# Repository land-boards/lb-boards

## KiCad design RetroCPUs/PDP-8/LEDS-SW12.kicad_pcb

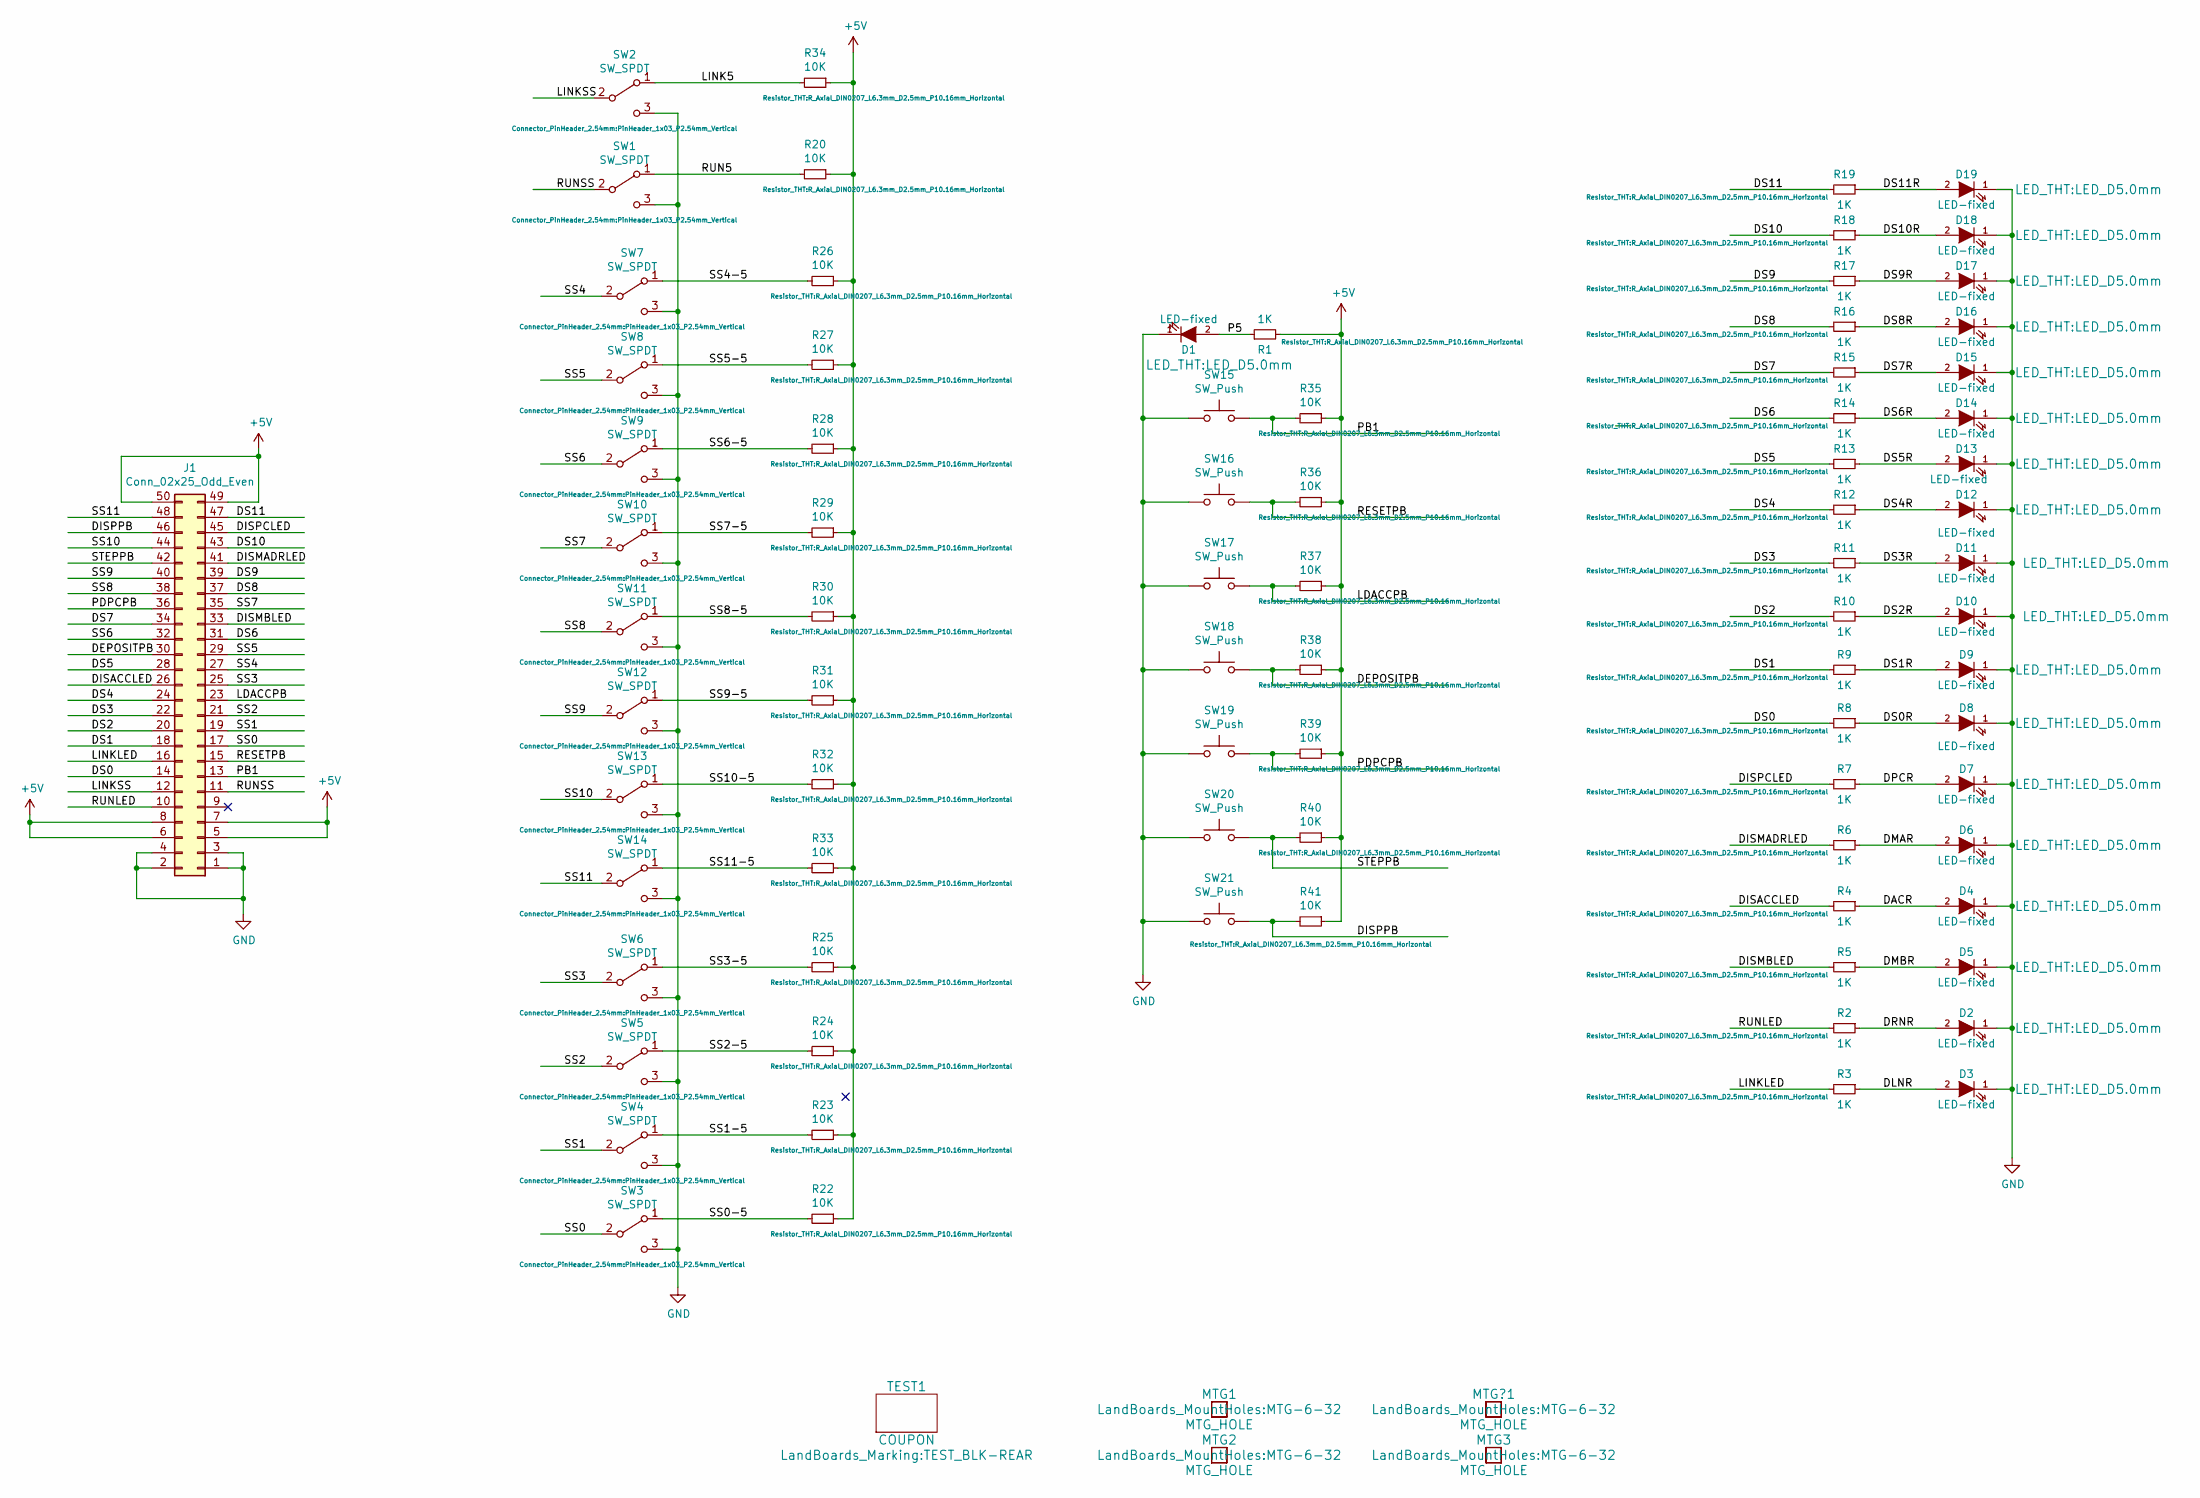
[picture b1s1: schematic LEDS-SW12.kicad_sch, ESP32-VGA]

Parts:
D1, D2, D3, D4, D5, D6, D7, D8, D9, D10, D11, D12, D13, D14, D15, D16, D17, D18, D19: LED-fixed; LED_D5.0mm
J1: Conn_02x25_Odd_Even; PinHeader_2x25_P2.54mm_Horizontal
MTG1, MTG2, MTG3: MTG_HOLE; MTG-6-32
MTG?1: MTG_HOLE; MTG-6-32
R1, R2, R3, R4, R5, R6, R7, R8, R9, R10, R11, R12, R13, R14, R15, R16, R17, R18, R19: 1K; R_Axial_DIN0207_L6.3mm_D2.5mm_P10.16mm_Horizontal
R20, R22, R23, R24, R25, R26, R27, R28, R29, R30, R31, R32, R33, R34, R35, R36, R37, R38, R39, R40, R41: 10K; R_Axial_DIN0207_L6.3mm_D2.5mm_P10.16mm_Horizontal
SW1, SW2, SW3, SW4, SW5, SW6, SW7, SW8, SW9, SW10, SW11, SW12, SW13, SW14: SW_SPDT; PinHeader_1x03_P2.54mm_Vertical
SW15, SW16, SW17, SW18, SW19, SW20, SW21: SW_Push; SW_PUSH_6mm_H8.5mm
TEST1: COUPON; TEST_BLK-REAR

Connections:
+5V: J1.5, J1.6, J1.7, J1.8, J1.49, J1.50, R1.2, R20.1, R22.1, R23.1, R24.1, R25.1, R26.1, R27.1, R28.1, R29.1, R30.1, R31.1, R32.1, R33.1, R34.1, R35.1, R36.1, R37.1, R38.1, R39.1, R40.1, R41.1
/DACR: D4.2 (A), R4.1
/DEPOSITPB: J1.30, R38.2, SW18.2
/DISACCLED: J1.26, R4.2
/DISMADRLED: J1.41, R6.2
/DISMBLED: J1.33, R5.2
/DISPCLED: J1.45, R7.2
/DISPPB: J1.46, R41.2, SW21.2
/DLNR: D3.2 (A), R3.1
/DMAR: D6.2 (A), R6.1
/DMBR: D5.2 (A), R5.1
/DPCR: D7.2 (A), R7.1
/DRNR: D2.2 (A), R2.1
/DS0: J1.14, R8.2
/DS0R: D8.2 (A), R8.1
/DS1: J1.18, R9.2
/DS1R: D9.2 (A), R9.1
/DS2: J1.20, R10.2
/DS2R: D10.2 (A), R10.1
/DS3: J1.22, R11.2
/DS3R: D11.2 (A), R11.1
/DS4: J1.24, R12.2
/DS4R: D12.2 (A), R12.1
/DS5: J1.28, R13.2
/DS5R: D13.2 (A), R13.1
/DS6: J1.31, R14.2
/DS6R: D14.2 (A), R14.1
/DS7: J1.34, R15.2
/DS7R: D15.2 (A), R15.1
/DS8: J1.37, R16.2
/DS8R: D16.2 (A), R16.1
/DS9: J1.39, R17.2
/DS9R: D17.2 (A), R17.1
/DS10: J1.43, R18.2
/DS10R: D18.2 (A), R18.1
/DS11: J1.47, R19.2
/DS11R: D19.2 (A), R19.1
/LDACCPB: J1.23, R37.2, SW17.2
/LINK5: R34.2, SW2.1 (A)
/LINKLED: J1.16, R3.2
/LINKSS: J1.12, SW2.2 (B)
/P5: D1.2 (A), R1.1
/PB1: J1.13, R35.2, SW15.2
/PDPCPB: J1.36, R39.2, SW19.2
/RESETPB: J1.15, R36.2, SW16.2
/RUN5: R20.2, SW1.1 (A)
/RUNLED: J1.10, R2.2
/RUNSS: J1.11, SW1.2 (B)
/SS0: J1.17, SW3.2 (B)
/SS0-5: R22.2, SW3.1 (A)
/SS1: J1.19, SW4.2 (B)
/SS1-5: R23.2, SW4.1 (A)
/SS2: J1.21, SW5.2 (B)
/SS2-5: R24.2, SW5.1 (A)
/SS3: J1.25, SW6.2 (B)
/SS3-5: R25.2, SW6.1 (A)
/SS4: J1.27, SW7.2 (B)
/SS4-5: R26.2, SW7.1 (A)
/SS5: J1.29, SW8.2 (B)
/SS5-5: R27.2, SW8.1 (A)
/SS6: J1.32, SW9.2 (B)
/SS6-5: R28.2, SW9.1 (A)
/SS7: J1.35, SW10.2 (B)
/SS7-5: R29.2, SW10.1 (A)
/SS8: J1.38, SW11.2 (B)
/SS8-5: R30.2, SW11.1 (A)
/SS9: J1.40, SW12.2 (B)
/SS9-5: R31.2, SW12.1 (A)
/SS10: J1.44, SW13.2 (B)
/SS10-5: R32.2, SW13.1 (A)
/SS11: J1.48, SW14.2 (B)
/SS11-5: R33.2, SW14.1 (A)
/STEPPB: J1.42, R40.2, SW20.2
GND: D1.1 (K), D2.1 (K), D3.1 (K), D4.1 (K), D5.1 (K), D6.1 (K), D7.1 (K), D8.1 (K), D9.1 (K), D10.1 (K), D11.1 (K), D12.1 (K), D13.1 (K), D14.1 (K), D15.1 (K), D16.1 (K), D17.1 (K), D18.1 (K), D19.1 (K), J1.1, J1.2, J1.3, J1.4, SW1.3 (C), SW2.3 (C), SW3.3 (C), SW4.3 (C), SW5.3 (C), SW6.3 (C), SW7.3 (C), SW8.3 (C), SW9.3 (C), SW10.3 (C), SW11.3 (C), SW12.3 (C), SW13.3 (C), SW14.3 (C), SW15.1, SW16.1, SW17.1, SW18.1, SW19.1, SW20.1, SW21.1

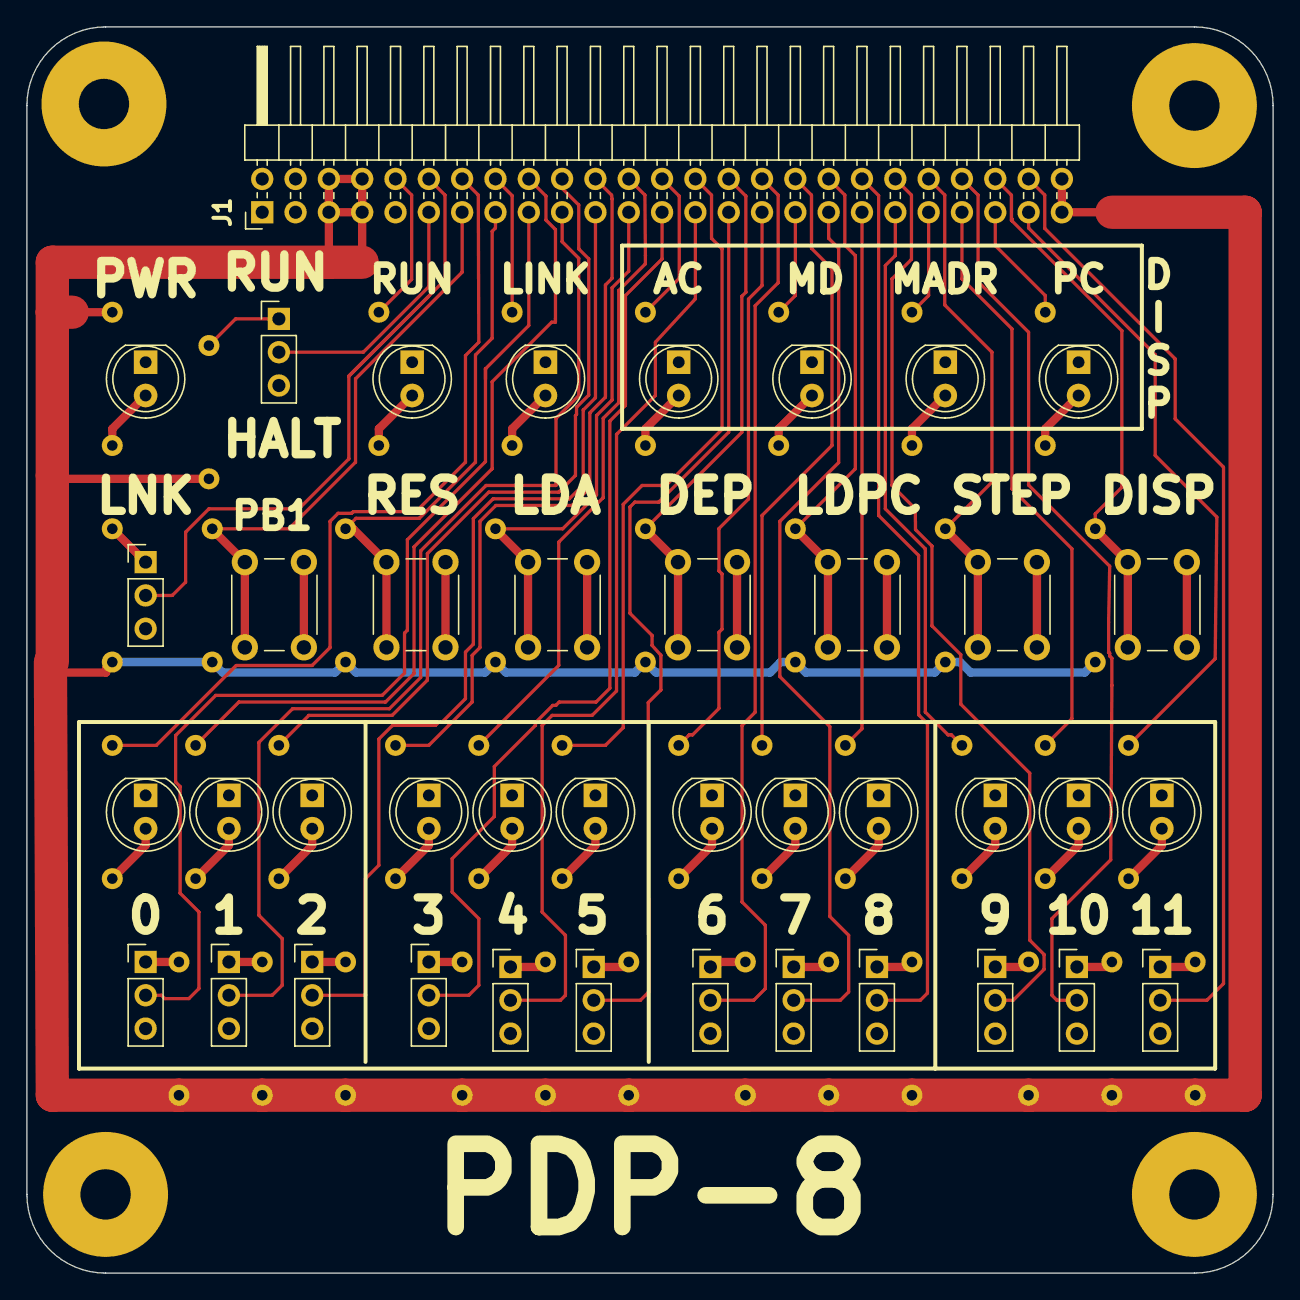
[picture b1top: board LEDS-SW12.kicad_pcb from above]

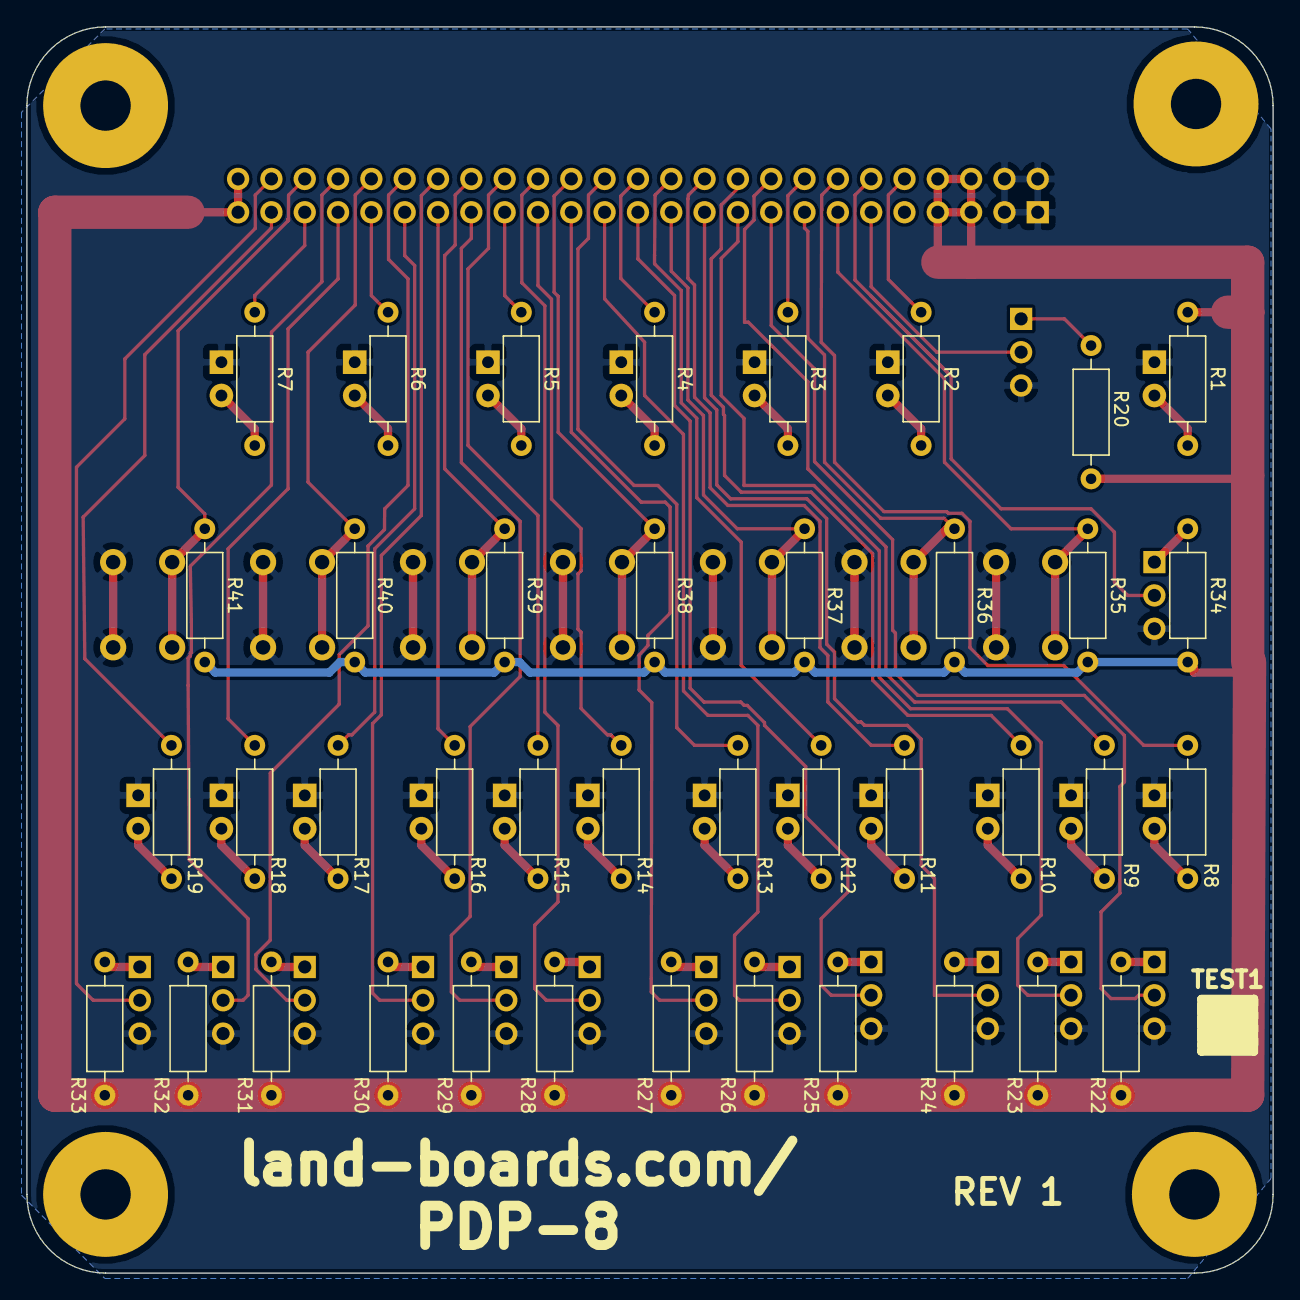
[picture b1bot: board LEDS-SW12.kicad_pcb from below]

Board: 2 copper layers, 95.0 x 95.0 mm, 86 parts (40 on the bottom side), 74 nets.

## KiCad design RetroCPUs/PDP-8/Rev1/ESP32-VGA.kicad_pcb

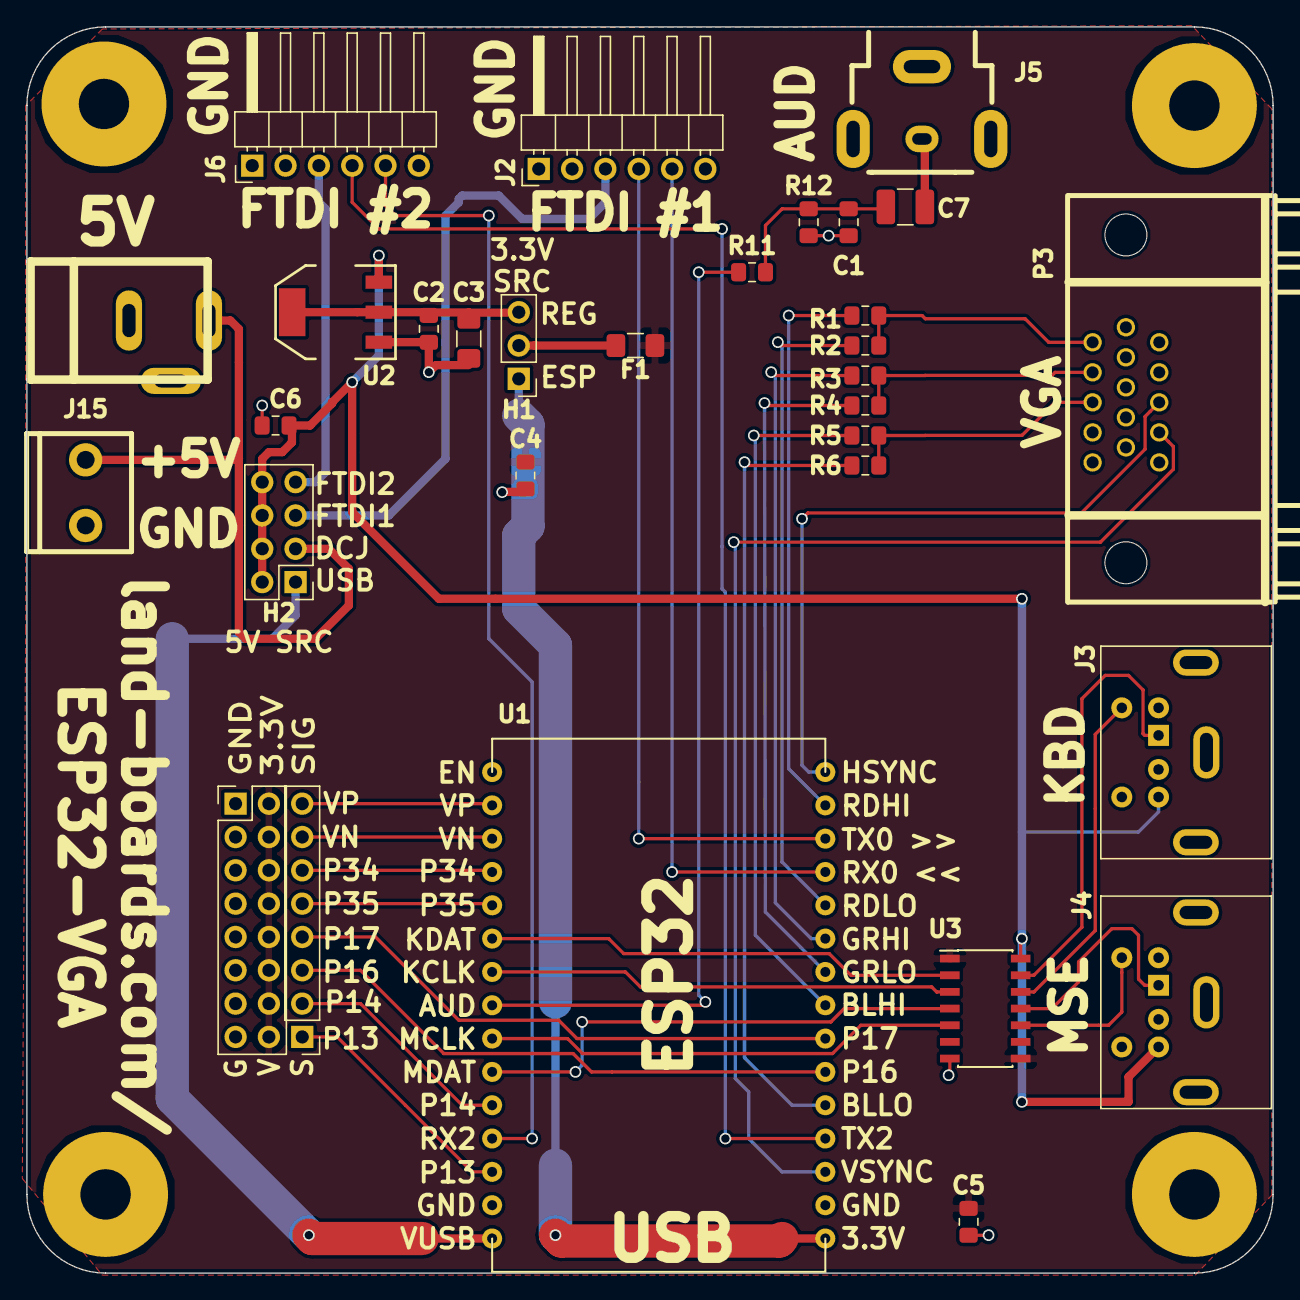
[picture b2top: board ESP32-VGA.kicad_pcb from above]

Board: 2 copper layers, 95.0 x 95.0 mm, 36 parts (0 on the bottom side), 44 nets.

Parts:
C1, C2, C4, C5, C6: 0.1uF; C_0805_2012Metric_Pad1.15x1.40mm_HandSolder
C3: 10uF; C_1206_3216Metric_Pad1.42x1.75mm_HandSolder
C7: 10uF; C_1210_3225Metric_Pad1.42x2.65mm_HandSolder
F1: Polyfuse_Small; Fuse_1206_3216Metric_Pad1.42x1.75mm_HandSolder
H1: Conn_01x03; PinHeader_1x03_P2.54mm_Vertical
H2: Conn_02x04_Odd_Even; PinHeader_2x04_P2.54mm_Vertical
J1: DCJ0202; DCJ-NEW-Slotted
J2, J6: FTDI; PinHeader_1x06_P2.54mm_Horizontal
J3, J4: PS2_DIN6; Connector_Mini-DIN_Female_6Pin_2rows
J5: RCA-JACK; RCA
J15: Conn_01x02; TB2-5MM
MTG1, MTG2, MTG3: MTG_HOLE; MTG-6-32
MTG?1: MTG_HOLE; MTG-6-32
P2: Conn_02x08_Odd_Even; PinHeader_2x08_P2.54mm_Vertical
P3: VGA; DB_15F-VGA-fixed
P4: Conn_01x08; PinHeader_1x08_P2.54mm_Vertical
R1, R3, R5: 422; R_0805_2012Metric_Pad1.15x1.40mm_HandSolder
R2, R4, R6: 845; R_0805_2012Metric_Pad1.15x1.40mm_HandSolder
R11: 261; R_0805_2012Metric_Pad1.15x1.40mm_HandSolder
R12: 150; R_0805_2012Metric_Pad1.15x1.40mm_HandSolder
TEST1: COUPON; TEST_BLK-REAR
U1: ESP32; ESP32_EXP
U2: AP1117; SOT223
U3: TXS0104; SOIC-14_3.9x8.7mm_P1.27mm

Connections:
+3V3: C4.1, C5.1, F1.1, P2.2, P2.4, P2.6, P2.8, P2.10, P2.12, P2.14, P2.16, U3.1, U3.8
+5V: C6.1, H2.2, H2.4, H2.6, H2.8, J3.4, J4.4, U2.3, U3.14
/AUDIO: R11.2, U1.23
/BLUHI: R5.2, U1.8
/BLULO: R6.2, U1.5
/DCIN: H2.3, J1.1, J15.2
/ESP3V: H1.1, U1.1
/FTDI5V0: H2.5, J2.3
/FTDI5V2: H2.7, J6.3
/GP13: P4.1, U1.28
/GP14: P4.2, U1.26
/GP16: P4.3, U1.6
/GP17: P4.4, U1.7
/GP34: P4.6, U1.19
/GP35: P4.5, U1.20
/GRNHI: R3.2, U1.10
/GRNLO: R4.2, U1.9
/HSYNC: P3.13, U1.15
/KBCLK: U1.22, U3.3
/KBDAT: U1.21, U3.2
/MSECLK: U1.24, U3.5
/MSEDAT: U1.25, U3.4
/REDHI: R1.2, U1.14
/REDLO: R2.2, U1.11
/RX0: J2.5, U1.12
/RX2: J6.5, U1.27
/TX0: J2.4, U1.13
/TX2: J6.4, U1.4
/VN: P4.7, U1.18
/VO3: C2.1, C3.1, H1.3, U2.2, U2.4
/VP: P4.8, U1.17
/VSYNC: P3.14, U1.3
/VUSB: H2.1, U1.30
GND: C1.2, C2.2, C3.2, C4.2, C5.2, C6.2, J1.2, J1.3, J2.1, J3.3, J4.3, J5.1, J5.2, J5.3, J6.1, J15.1, P2.1, P2.3, P2.5, P2.7, P2.9, P2.11, P2.13, P2.15, P3.5, P3.6, P3.7, P3.8, P3.10, R12.1, U1.2, U1.29, U2.1, U3.7
unnamed: C1.1, C7.1, R11.1, R12.2
unnamed: C7.2, J5.4
unnamed: F1.2, H1.2
unnamed: J3.1, U3.13
unnamed: J3.5, U3.12
unnamed: J4.1, U3.11
unnamed: J4.5, U3.10
unnamed: P3.1, R1.1, R2.1
unnamed: P3.2, R3.1, R4.1
unnamed: P3.3, R5.1, R6.1

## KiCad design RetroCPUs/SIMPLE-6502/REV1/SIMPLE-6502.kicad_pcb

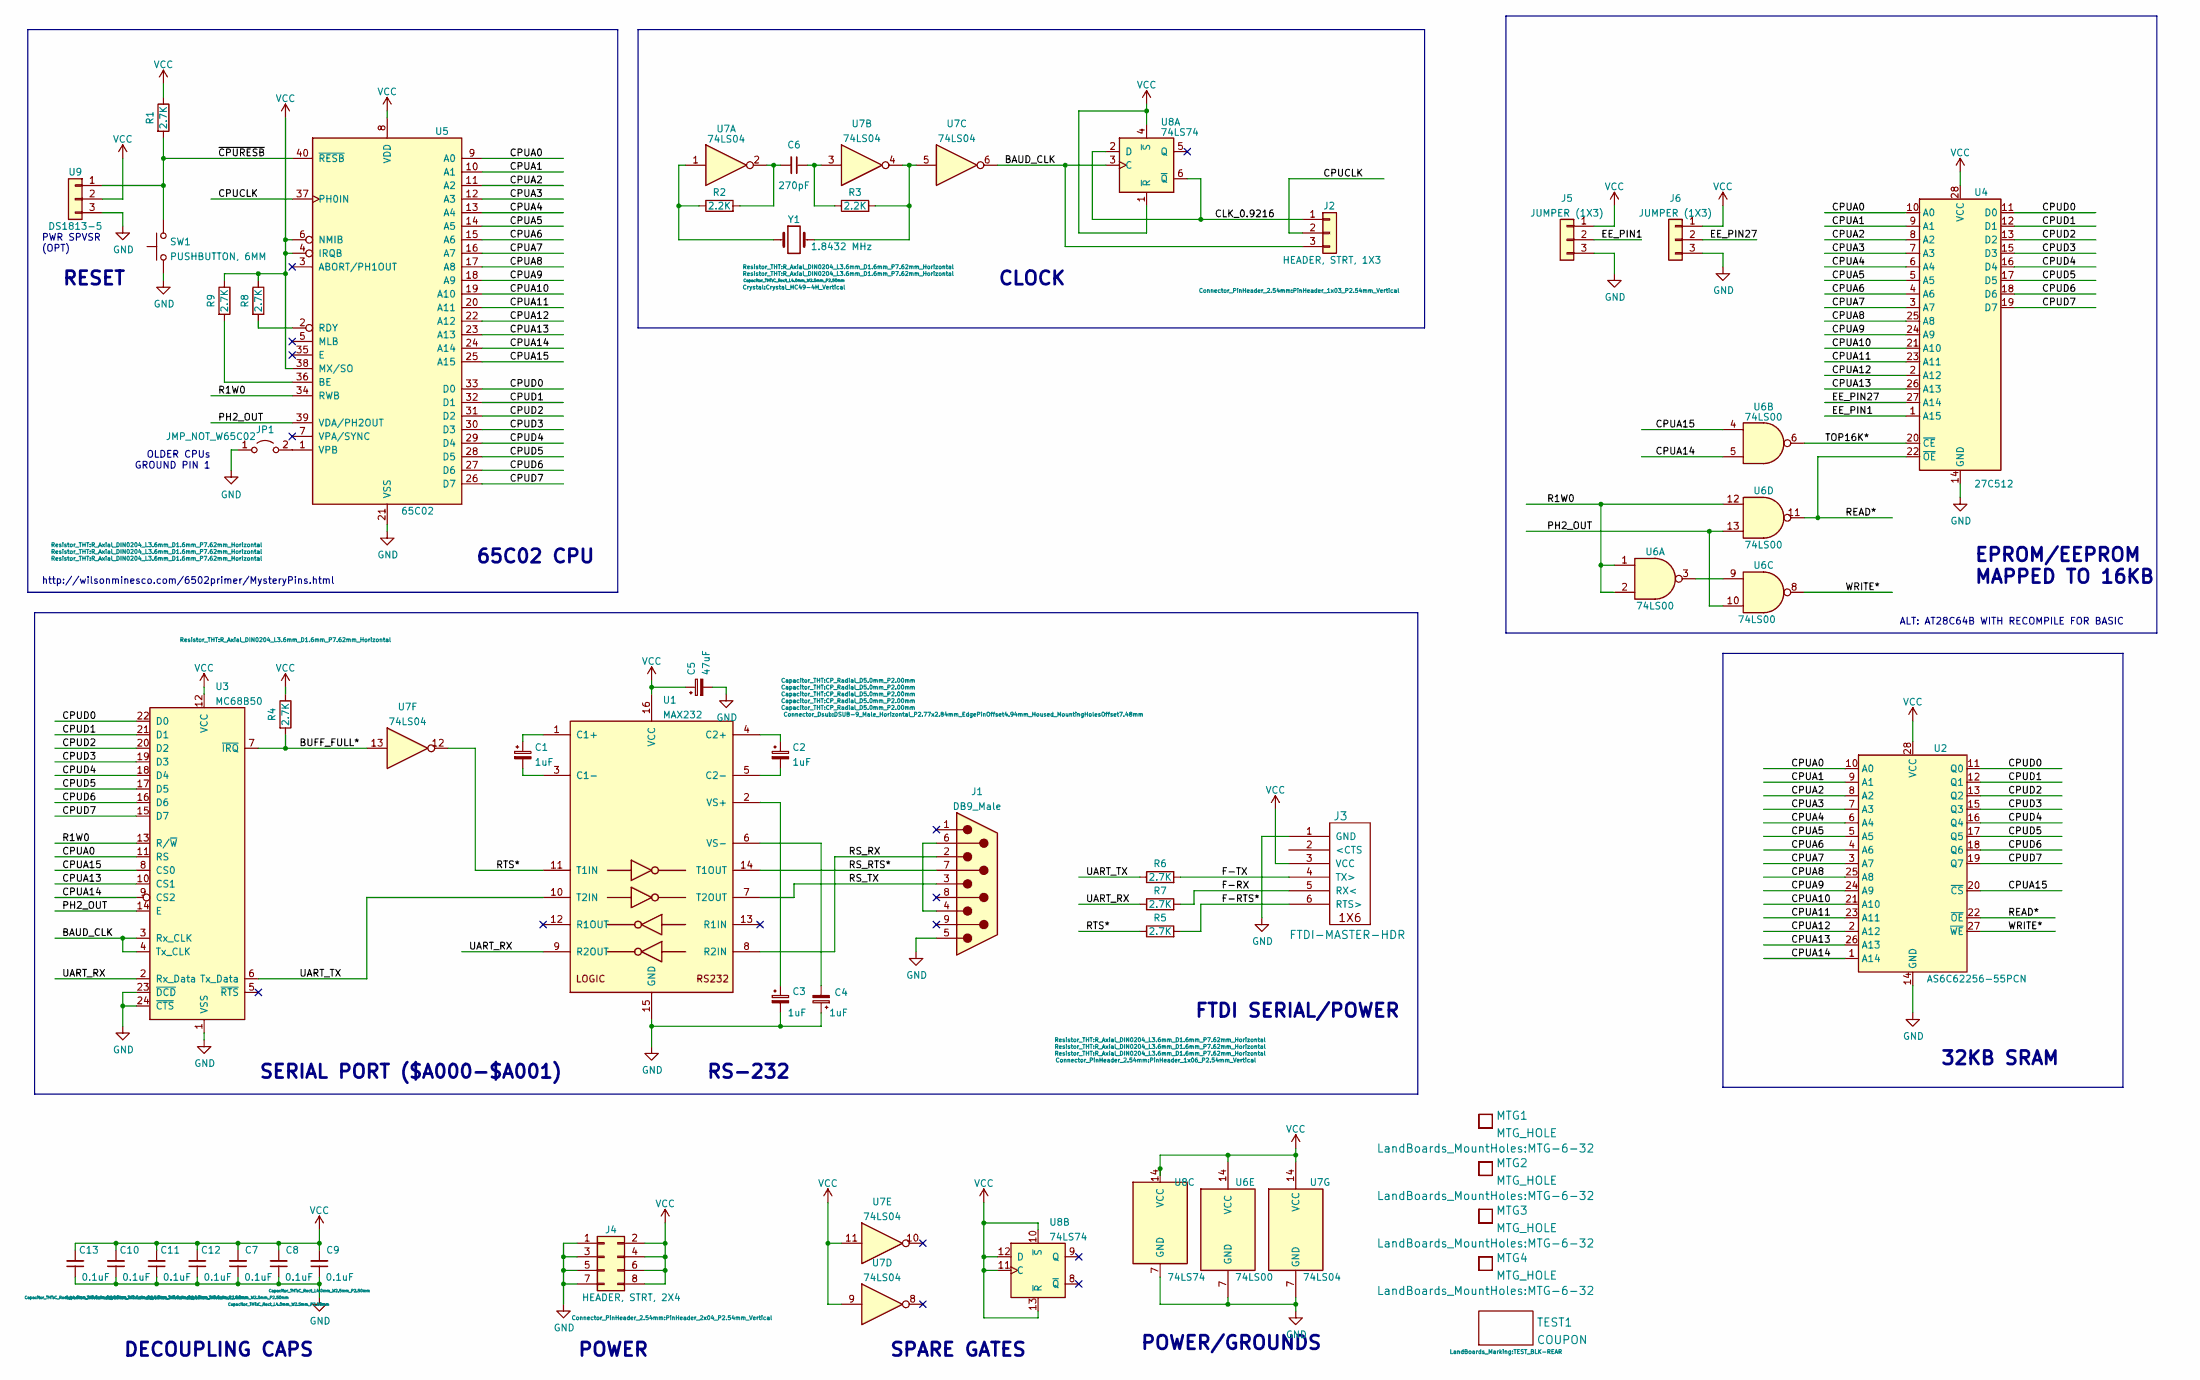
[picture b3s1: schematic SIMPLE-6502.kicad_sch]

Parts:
C1, C2, C3, C4: 1uF; CP_Radial_D5.0mm_P2.00mm
C5: 47uF; CP_Radial_D5.0mm_P2.00mm
C6: 270pF; C_Rect_L4.0mm_W2.5mm_P2.50mm
C7, C8, C9, C10, C11, C12, C13: 0.1uF; C_Rect_L4.0mm_W2.5mm_P2.50mm
J1: DB9_Male; DSUB-9_Male_Horizontal_P2.77x2.84mm_EdgePinOffset4.94mm_Hou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
J2: HEADER, STRT, 1X3; PinHeader_1x03_P2.54mm_Vertical
J3: FTDI-MASTER-HDR; PinHeader_1x06_P2.54mm_Vertical
J4: HEADER, STRT, 2X4; PinHeader_2x04_P2.54mm_Vertical
J5, J6: JUMPER (1X3); PinHeader_1x03_P2.54mm_Vertical
JP1: JMP_NOT_W65C02; PinHeader_1x02_P2.54mm_Vertical
MTG1, MTG2, MTG3, MTG4: MTG_HOLE; MTG-6-32
R1, R4, R5, R6, R7, R8, R9: 2.7K; R_Axial_DIN0204_L3.6mm_D1.6mm_P7.62mm_Horizontal
R2, R3: 2.2K; R_Axial_DIN0204_L3.6mm_D1.6mm_P7.62mm_Horizontal
SW1: PUSHBUTTON, 6MM; SW_PUSH_6mm_H8.5mm
TEST1: COUPON; TEST_BLK-REAR
U1: MAX232; DIP-16_W7.62mm_LongPads
U2: AS6C62256-55PCN; DIP-28_W15.24mm
U3: MC68B50; DIP-24_W15.24mm
U4: 27C512; DIP-28_W15.24mm
U5: 65C02; DIP-40_W15.24mm_LongPads
U6: 74LS00; DIP-14_W7.62mm_LongPads
U7: 74LS04; DIP-14_W7.62mm_LongPads
U8: 74LS74; DIP-14_W7.62mm_LongPads
U9: DS1813-5; TO-92
Y1: 1.8432 MHz; Crystal_HC49-4H_Vertical

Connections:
/BAUD_CLK: J2.3, U3.3 (Rx_CLK), U3.4 (Tx_CLK), U7.6, U8.3 (C)
/BUFF_FULL*: R4.2, U3.7 (~IRQ), U7.13
/CLK_0.9216: J2.1, U8.2 (D), U8.6 (~Q)
/CPUA0: U2.10 (A0), U3.11 (RS), U4.10 (A0), U5.9 (A0)
/CPUA1: U2.9 (A1), U4.9 (A1), U5.10 (A1)
/CPUA2: U2.8 (A2), U4.8 (A2), U5.11 (A2)
/CPUA3: U2.7 (A3), U4.7 (A3), U5.12 (A3)
/CPUA4: U2.6 (A4), U4.6 (A4), U5.13 (A4)
/CPUA5: U2.5 (A5), U4.5 (A5), U5.14 (A5)
/CPUA6: U2.4 (A6), U4.4 (A6), U5.15 (A6)
/CPUA7: U2.3 (A7), U4.3 (A7), U5.16 (A7)
/CPUA8: U2.25 (A8), U4.25 (A8), U5.17 (A8)
/CPUA9: U2.24 (A9), U4.24 (A9), U5.18 (A9)
/CPUA10: U2.21 (A10), U4.21 (A10), U5.19 (A10)
/CPUA11: U2.23 (A11), U4.23 (A11), U5.20 (A11)
/CPUA12: U2.2 (A12), U4.2 (A12), U5.22 (A12)
/CPUA13: U2.26 (A13), U3.10 (CS1), U4.26 (A13), U5.23 (A13)
/CPUA14: U2.1 (A14), U3.9 (CS2), U5.24 (A14), U6.5
/CPUA15: U2.20 (~CS), U3.8 (CS0), U5.25 (A15), U6.4
/CPUCLK: J2.2, U5.37 (PH0IN)
/CPUD0: U2.11 (Q0), U3.22 (D0), U4.11 (D0), U5.33 (D0)
/CPUD1: U2.12 (Q1), U3.21 (D1), U4.12 (D1), U5.32 (D1)
/CPUD2: U2.13 (Q2), U3.20 (D2), U4.13 (D2), U5.31 (D2)
/CPUD3: U2.15 (Q3), U3.19 (D3), U4.15 (D3), U5.30 (D3)
/CPUD4: U2.16 (Q4), U3.18 (D4), U4.16 (D4), U5.29 (D4)
/CPUD5: U2.17 (Q5), U3.17 (D5), U4.17 (D5), U5.28 (D5)
/CPUD6: U2.18 (Q6), U3.16 (D6), U4.18 (D6), U5.27 (D6)
/CPUD7: U2.19 (Q7), U3.15 (D7), U4.19 (D7), U5.26 (D7)
/EE_PIN1: J5.2, U4.1 (A15)
/EE_PIN27: J6.2, U4.27 (A14)
/F-RTS*: J3.6 (CTS>), R5.2
/F-RX: J3.5 (TX<), R7.2
/F-TX: J3.4 (RX>), R6.2
/PH2_OUT: U3.14 (E), U5.39 (VDA/PH2OUT), U6.10, U6.13
/R1W0: U3.13 (R/~W), U5.34 (RWB), U6.1, U6.2, U6.12
/READ*: U2.22 (~OE), U4.22 (~OE), U6.11
/RS_RTS*: J1.7, U1.14 (T1OUT)
/RS_RX: J1.2, U1.8 (R2IN)
/RS_TX: J1.3, U1.7 (T2OUT)
/RTS*: R5.1, U1.11 (T1IN), U7.12
/TOP16K*: U4.20 (~CE), U6.6
/UART_RX: R7.1, U1.9 (R2OUT), U3.2 (Rx_Data)
/UART_TX: R6.1, U1.10 (T2IN), U3.6 (Tx_Data)
/WRITE*: U2.27 (~WE), U6.8
/~CPURESB: R1.2, SW1.2, U5.40 (~RESB), U9.1
GND: C3.2, C4.1, C5.2, C7.1, C8.1, C9.1, C10.1, C11.1, C12.1, C13.1, J1.5, J3.1 (GND), J4.1, J4.3, J4.5, J4.7, J5.3, J6.3, JP1.1 (A), SW1.1, U1.15 (GND), U2.14 (GND), U3.1 (VSS), U3.23 (~DCD), U3.24 (~CTS), U4.14 (GND), U5.21 (VSS), U6.7 (GND), U7.7 (GND), U8.7 (GND), U9.3
unnamed: C6.1, R3.1, U7.3
unnamed: C6.2, R2.2, U7.2
unnamed: J1.4, J1.6
unnamed: JP1.2 (B), U5.1 (VPB)
unnamed: R2.1, U7.1, Y1.1
unnamed: R3.2, U7.4, U7.5, Y1.2
unnamed: C1.1, U1.1 (C1+)
unnamed: C1.2, U1.3 (C1-)
unnamed: C2.1, U1.4 (C2+)
unnamed: C2.2, U1.5 (C2-)
unnamed: C3.1, U1.2 (VS+)
unnamed: C4.2, U1.6 (VS-)
unnamed: R9.2, U5.36 (BE)
unnamed: R8.2, U5.2 (RDY)
unnamed: U6.3, U6.9
VCC: C5.1, C7.2, C8.2, C9.2, C10.2, C11.2, C12.2, C13.2, J3.3 (VCC), J4.2, J4.4, J4.6, J4.8, J5.1, J6.1, R1.1, R4.1, R8.1, R9.1, U1.16 (VCC), U2.28 (VCC), U3.12 (VCC), U4.28 (VCC), U5.4 (IRQB), U5.6 (NMIB), U5.8 (VDD), U5.38 (MX/SO), U6.14 (VCC), U7.9, U7.11, U7.14 (VCC), U8.1 (~R), U8.4 (~S), U8.10 (~S), U8.11 (C), U8.12 (D), U8.13 (~R), U8.14 (VCC), U9.2

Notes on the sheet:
POWER
RESET
32KB SRAM
DECOUPLING CAPS
ALT: AT28C64B WITH RECOMPILE FOR BASIC
SPARE GATES
FTDI SERIAL/POWER
OLDER CPUs GROUND PIN 1
PWR SPVSR (OPT)
SERIAL PORT ($A000-$A001)
POWER/GROUNDS
http://wilsonminesco.com/6502primer/MysteryPins.html
65C02 CPU
EPROM/EEPROM MAPPED TO 16KB
CLOCK
RS-232

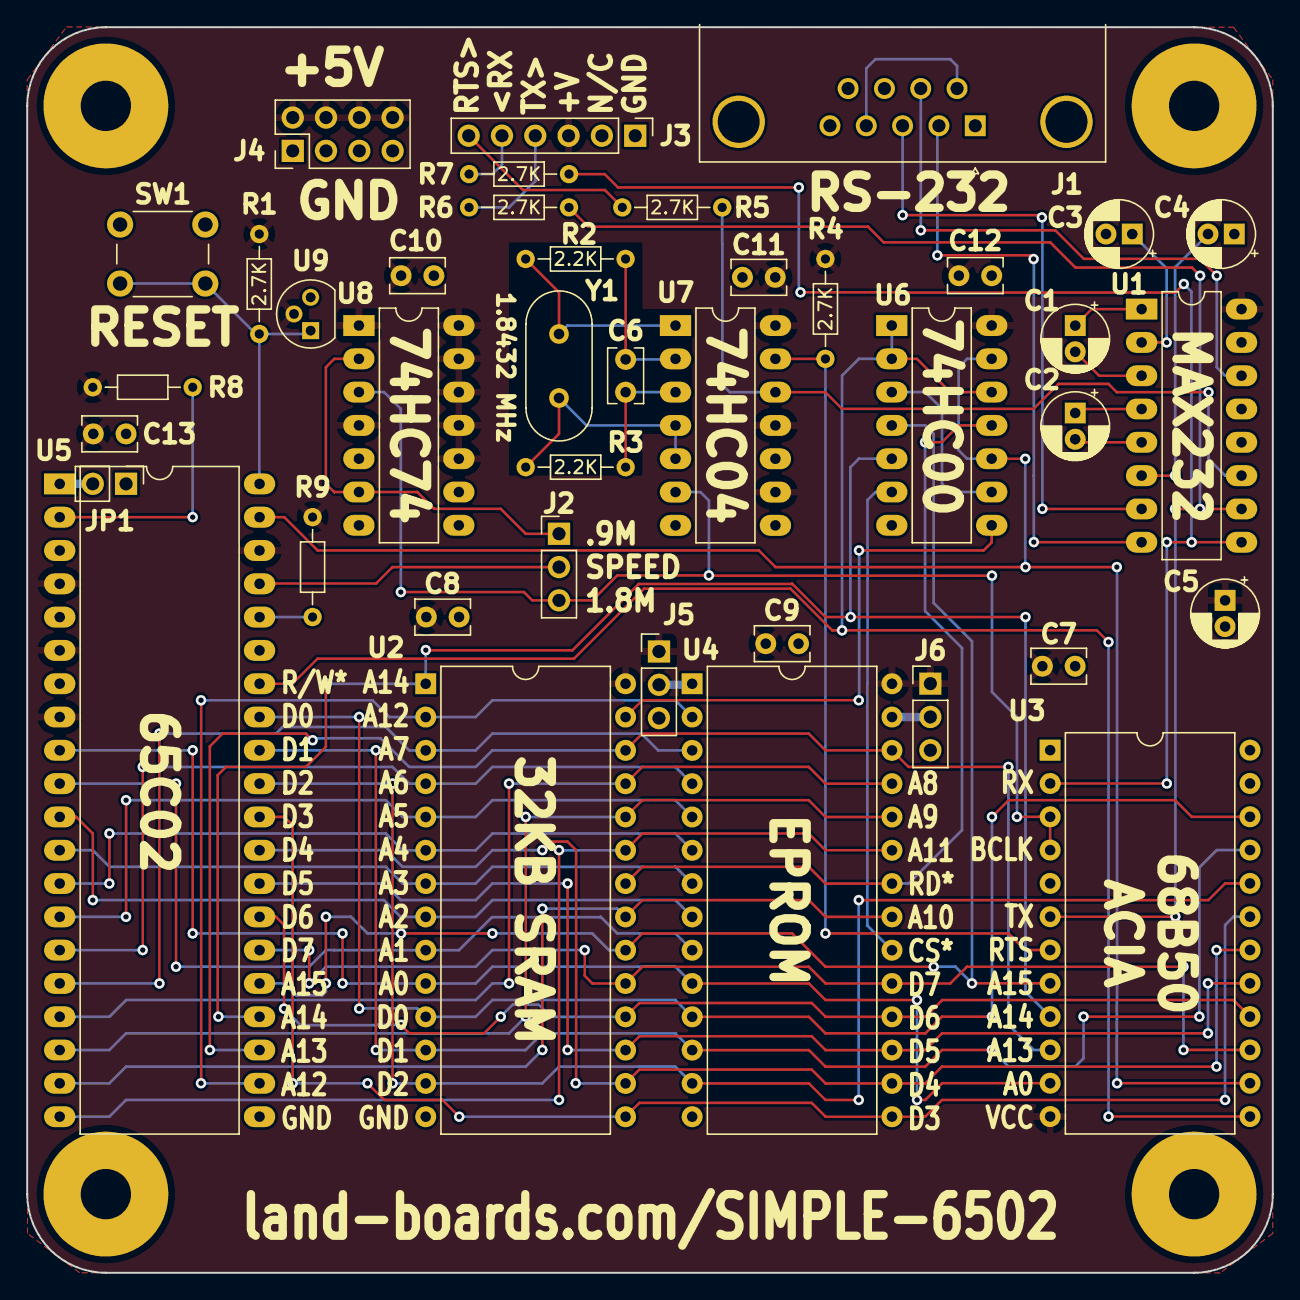
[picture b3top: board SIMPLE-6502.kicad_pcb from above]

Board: 2 copper layers, 95.0 x 95.0 mm, 45 parts (0 on the bottom side), 62 nets.

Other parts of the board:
TEST: COUPON; TEST_BLK-REAR
